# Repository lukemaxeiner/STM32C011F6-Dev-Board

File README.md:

# STM32C011F6-Dev-Board
A development board for the STM32C011F6 for use on a breadboard. It has power regulation, SWD programming capabilities, a reset button, and power LED. All GPIO pins are put to a broken out header pin. Resistors are added on SWD pins to improve signal integrety, allowing for more versatility in its usage.

The input voltage pin accepts between 3.3 and 15V, and the microcontroller can run on an input voltage as low as 2V4. The microcontroller runs on 3V3 GPIO signals and power under optimal conditions. Across all output pins and power pins, the total power draw through the VCC pin is 3.3 Watts, and the total current draw out of any individual pin is 20mA.

This board is 0.84"x1.14", and fits on a breadboard when male pin headers are soldered onto the board. 

Below is the schematic for the dev board, created in KiCad 9.0

Fully rendered image of the PCB design

PCB design file

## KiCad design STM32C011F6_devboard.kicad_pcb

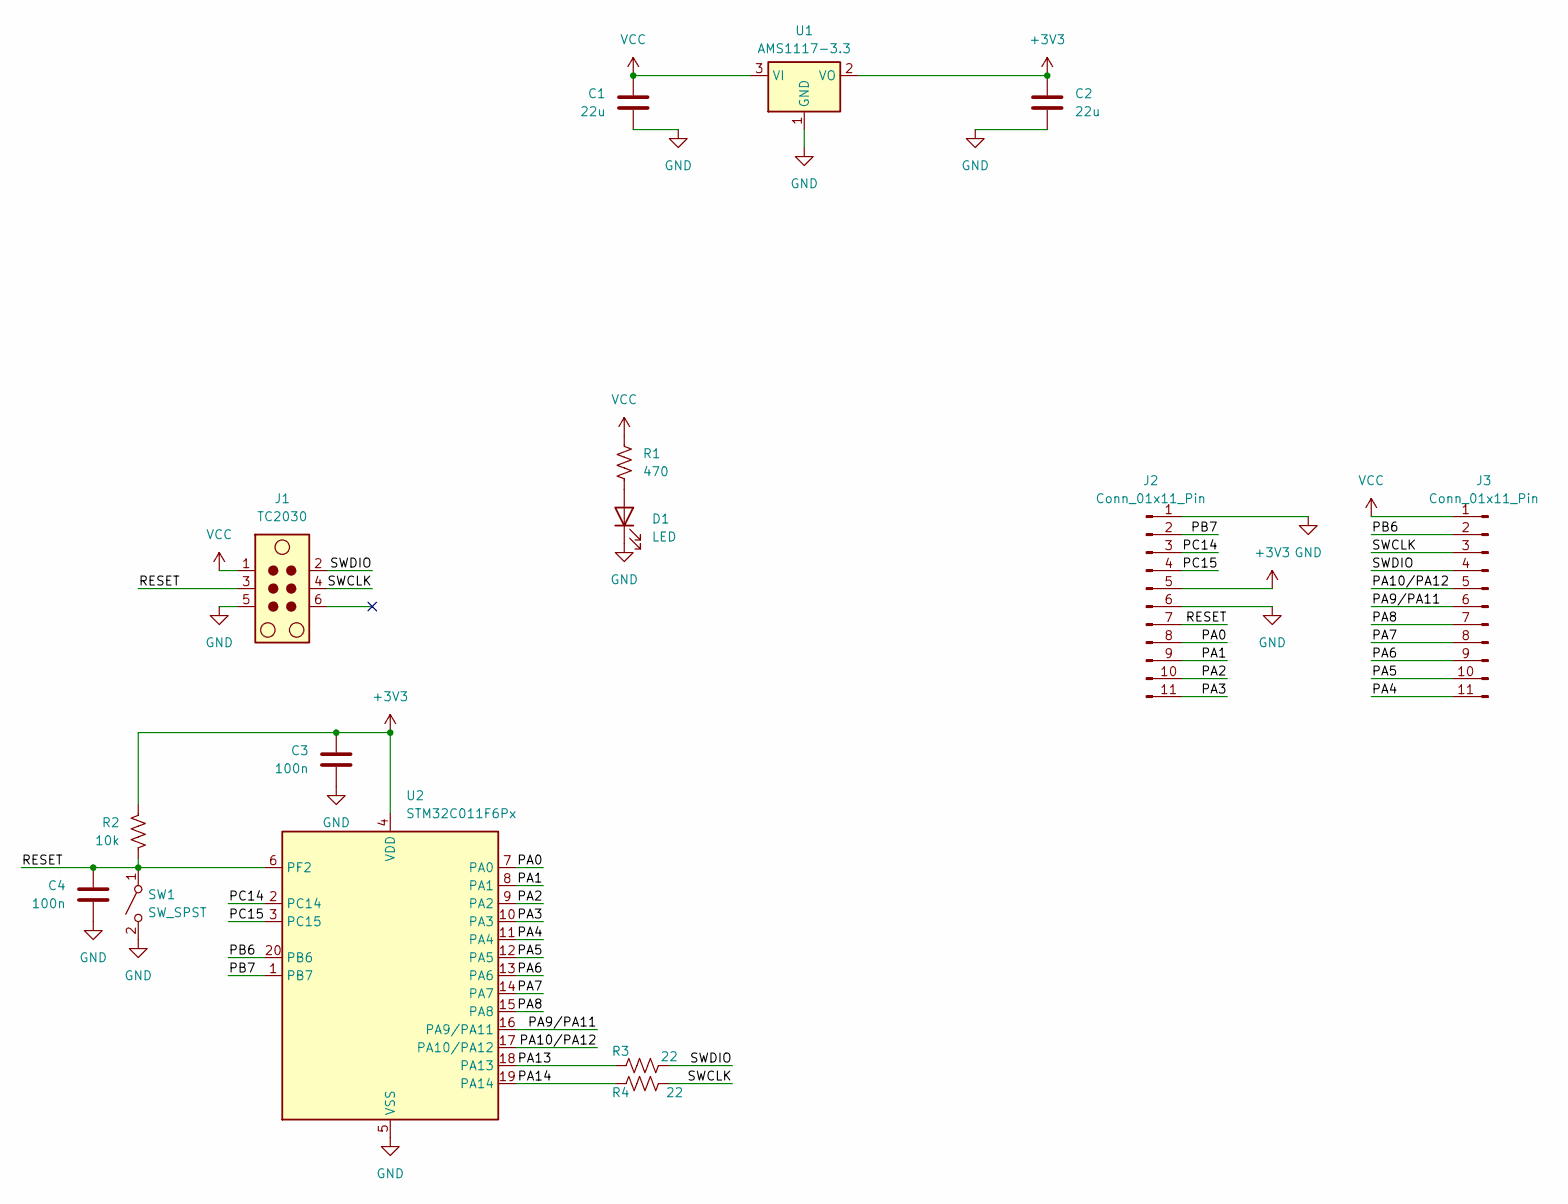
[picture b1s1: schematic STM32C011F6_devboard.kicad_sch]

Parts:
C1, C2: 22u; C_0603_1608Metric
C3, C4: 100n; C_0402_1005Metric
D1: LED; LED_0603_1608Metric
J1: TC2030; Tag-Connect_TC2030-IDC-NL_2x03_P1.27mm_Vertical
J2, J3: Conn_01x11_Pin; PinHeader_1x11_P2.54mm_Vertical
R1: 470; R_0402_1005Metric
R2: 10k; R_0402_1005Metric
R3, R4: 22; R_0402_1005Metric
SW1: SW_SPST; SW_SPST_B3U-1000P-B
U1: AMS1117-3.3; SOT-223-3_TabPin2
U2: STM32C011F6Px; TSSOP-20_4.4x6.5mm_P0.65mm

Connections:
+3V3: C2.1, C3.1, J2.5, R2.1, U1.2 (VO), U2.4 (VDD)
/PA0: J2.8, U2.7 (PA0)
/PA1: J2.9, U2.8 (PA1)
/PA2: J2.10, U2.9 (PA2)
/PA3: J2.11, U2.10 (PA3)
/PA4: J3.11, U2.11 (PA4)
/PA5: J3.10, U2.12 (PA5)
/PA6: J3.9, U2.13 (PA6)
/PA7: J3.8, U2.14 (PA7)
/PA8: J3.7, U2.15 (PA8)
/PA9/PA11: J3.6, U2.16 (PA9/PA11)
/PA10/PA12: J3.5, U2.17 (PA10/PA12)
/PA13: R3.1, U2.18 (PA13)
/PA14: R4.1, U2.19 (PA14)
/PB6: J3.2, U2.20 (PB6)
/PB7: J2.2, U2.1 (PB7)
/PC14: J2.3, U2.2 (PC14)
/PC15: J2.4, U2.3 (PC15)
/RESET: C4.1, J1.3, J2.7, R2.2, SW1.1 (A), U2.6 (PF2)
/SWCLK: J1.4, J3.3, R4.2
/SWDIO: J1.2, J3.4, R3.2
GND: C1.2, C2.2, C3.2, C4.2, D1.1 (K), J1.5, J2.1, J2.6, SW1.2 (B), U1.1 (GND), U2.5 (VSS)
unnamed: D1.2 (A), R1.2
VCC: C1.1, J1.1, J3.1, R1.1, U1.3 (VI)

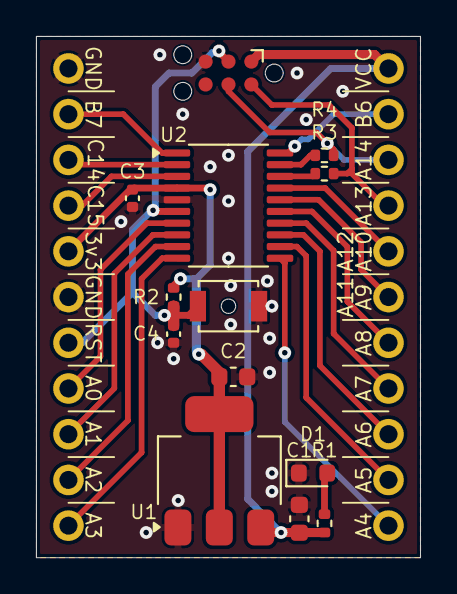
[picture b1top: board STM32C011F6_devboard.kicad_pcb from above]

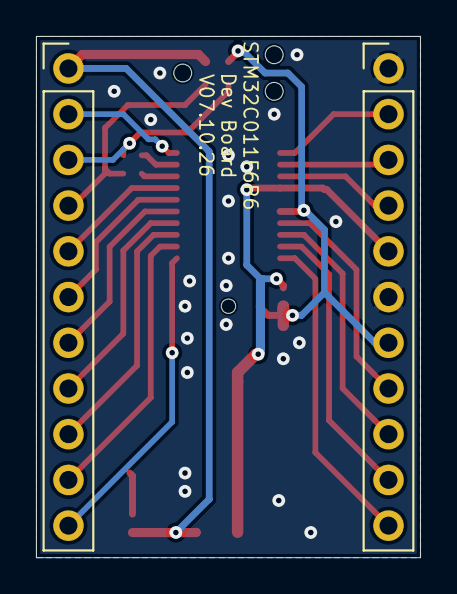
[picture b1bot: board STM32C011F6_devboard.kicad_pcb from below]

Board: 2 copper layers, 21.3 x 29.0 mm, 15 parts (2 on the bottom side), 24 nets.
